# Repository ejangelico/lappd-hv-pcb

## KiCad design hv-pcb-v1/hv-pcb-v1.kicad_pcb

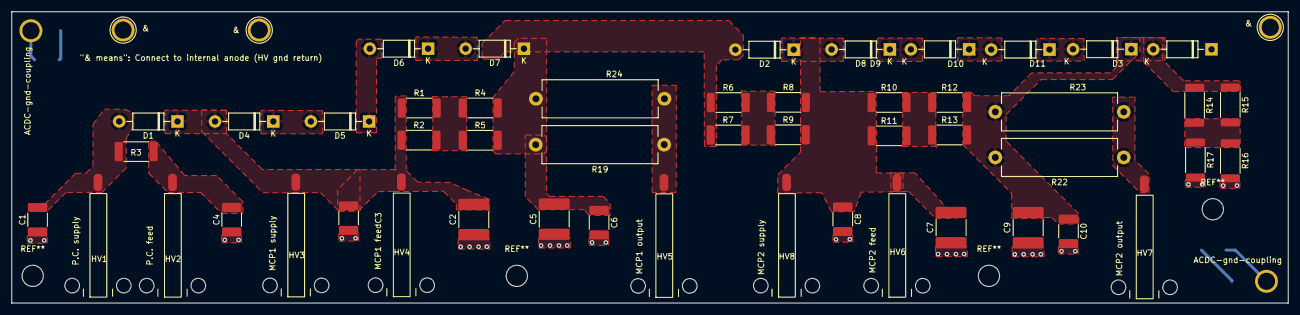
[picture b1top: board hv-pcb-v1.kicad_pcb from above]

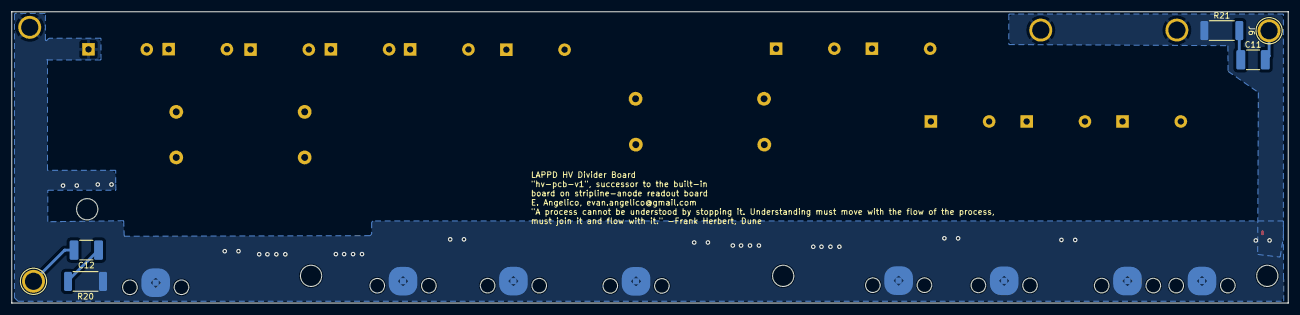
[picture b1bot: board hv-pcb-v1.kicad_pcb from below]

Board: 2 copper layers, 222.6 x 50.8 mm, 59 parts (6 on the bottom side), 22 nets.

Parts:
C1, C4: 100 pF; C_1812_4532Metric_Pad1.57x3.40mm_HandSolder
C2, C5, C7, C9: 1 nF; C_2220_5650Metric_Pad1.97x5.40mm_HandSolder
C3, C6, C8, C10, C11, C12: 10 pF; C_1812_4532Metric_Pad1.57x3.40mm_HandSolder
D1, D2, D3, D4, D5, D6, D8, D9, D10: Zener 200V; D_DO-41_SOD81_P10.16mm_Horizontal
D7, D11: Zener 150V; D_DO-41_SOD81_P10.16mm_Horizontal
HV1, HV2, HV3, HV4, HV5, HV6, HV7, HV8: Conn_01x02; SHV_cable_interface
J1, J2, J3, J6, J7: Conn_01x01_Socket; TestPoint_Plated_Hole_D3.0mm
R1, R2, R4, R5, R6, R7, R8, R9, R10, R11, R12, R13, R14, R15, R16, R17, R20, R21: R; R_2512_6332Metric_Pad1.40x3.35mm_HandSolder
R3: 100k; R_2512_6332Metric_Pad1.40x3.35mm_HandSolder
R19, R22: 10k; R_Axial_Power_L20.0mm_W6.4mm_P22.40mm
R23, R24: 1M; R_Axial_Power_L20.0mm_W6.4mm_P22.40mm

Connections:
/cath-in: C1.2, D1.2 (A), HV1.1, R3.1
/cath_out: C4.2, HV2.1, R3.2
/mcp1input: C2.2, C3.1, D1.1 (K), D4.2 (A), HV3.1, HV4.1, R1.1, R2.1
/mcp1output: HV5.1, R19.1, R24.1
/mcp2input: C7.2, C8.1, D2.1 (K), D8.2 (A), HV6.1, HV8.1, R8.2, R9.2, R10.1, R11.1
/mcp2output: HV7.1, R22.1, R23.1
/supply-gnd: C1.1, C2.1, C3.2, C4.1, C5.1, C6.2, C7.1, C8.2, C9.1, C10.2, D3.1 (K), HV1.2, HV2.2, HV3.2, HV4.2, HV5.2, HV6.2, HV7.2, HV8.2, J1.1, J2.1, J3.1, R16.2, R17.2, R20.1, R21.1
unnamed: C11.1, R21.2
unnamed: C12.1, R20.2
unnamed: C5.2, C6.1, D2.2 (A), D7.1 (K), R4.2, R5.2, R6.1, R7.1, R19.2, R24.2
unnamed: D4.1 (K), D5.2 (A)
unnamed: D5.1 (K), D6.2 (A)
unnamed: D6.1 (K), D7.2 (A)
unnamed: D8.1 (K), D9.2 (A)
unnamed: D9.1 (K), D10.2 (A)
unnamed: D10.1 (K), D11.2 (A)
unnamed: C9.2, C10.1, D3.2 (A), D11.1 (K), R12.2, R13.2, R14.1, R15.1, R22.2, R23.2
unnamed: C11.2, C12.2, J6.1, J7.1
unnamed: R1.2, R2.2, R4.1, R5.1
unnamed: R6.2, R7.2, R8.1, R9.1
unnamed: R10.2, R11.2, R12.1, R13.1
unnamed: R14.2, R15.2, R16.1, R17.1

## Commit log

2024-05-28 First commit - as produced v1 board
